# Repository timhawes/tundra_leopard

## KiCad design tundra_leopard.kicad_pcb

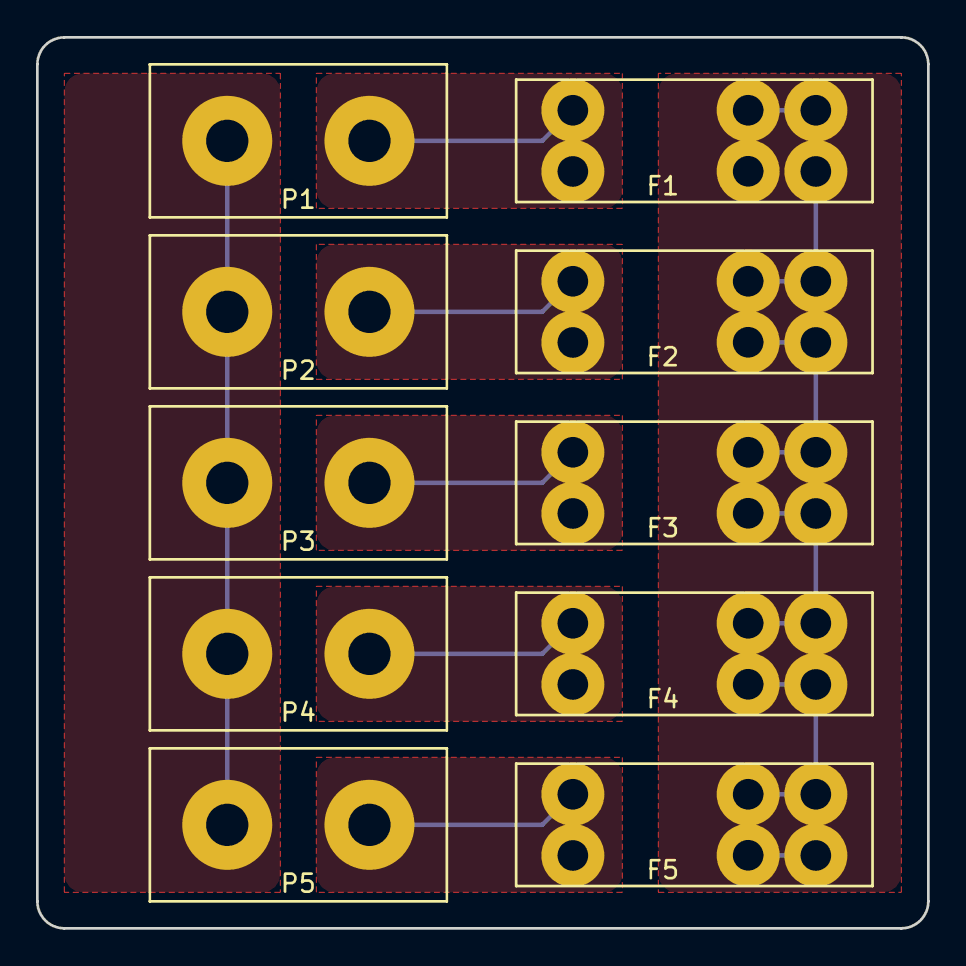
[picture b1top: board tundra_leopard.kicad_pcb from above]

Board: 2 copper layers, 49.5 x 49.5 mm, 10 parts (0 on the bottom side), 7 nets.

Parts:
F1, F2, F3, F4, F5: FUSE; KEYSTONE_3557_UNIVERSAL_FUSE_CLIP
P1, P2, P3, P4, P5: CONN_01X02; POWERPOLE_01X02

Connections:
unnamed: F1.1, P1.2
unnamed: F1.2, F2.2, F3.2, F4.2, F5.2
unnamed: F2.1, P2.2
unnamed: F3.1, P3.2
unnamed: F4.1, P4.2
unnamed: F5.1, P5.2
unnamed: P1.1, P2.1, P3.1, P4.1, P5.1
